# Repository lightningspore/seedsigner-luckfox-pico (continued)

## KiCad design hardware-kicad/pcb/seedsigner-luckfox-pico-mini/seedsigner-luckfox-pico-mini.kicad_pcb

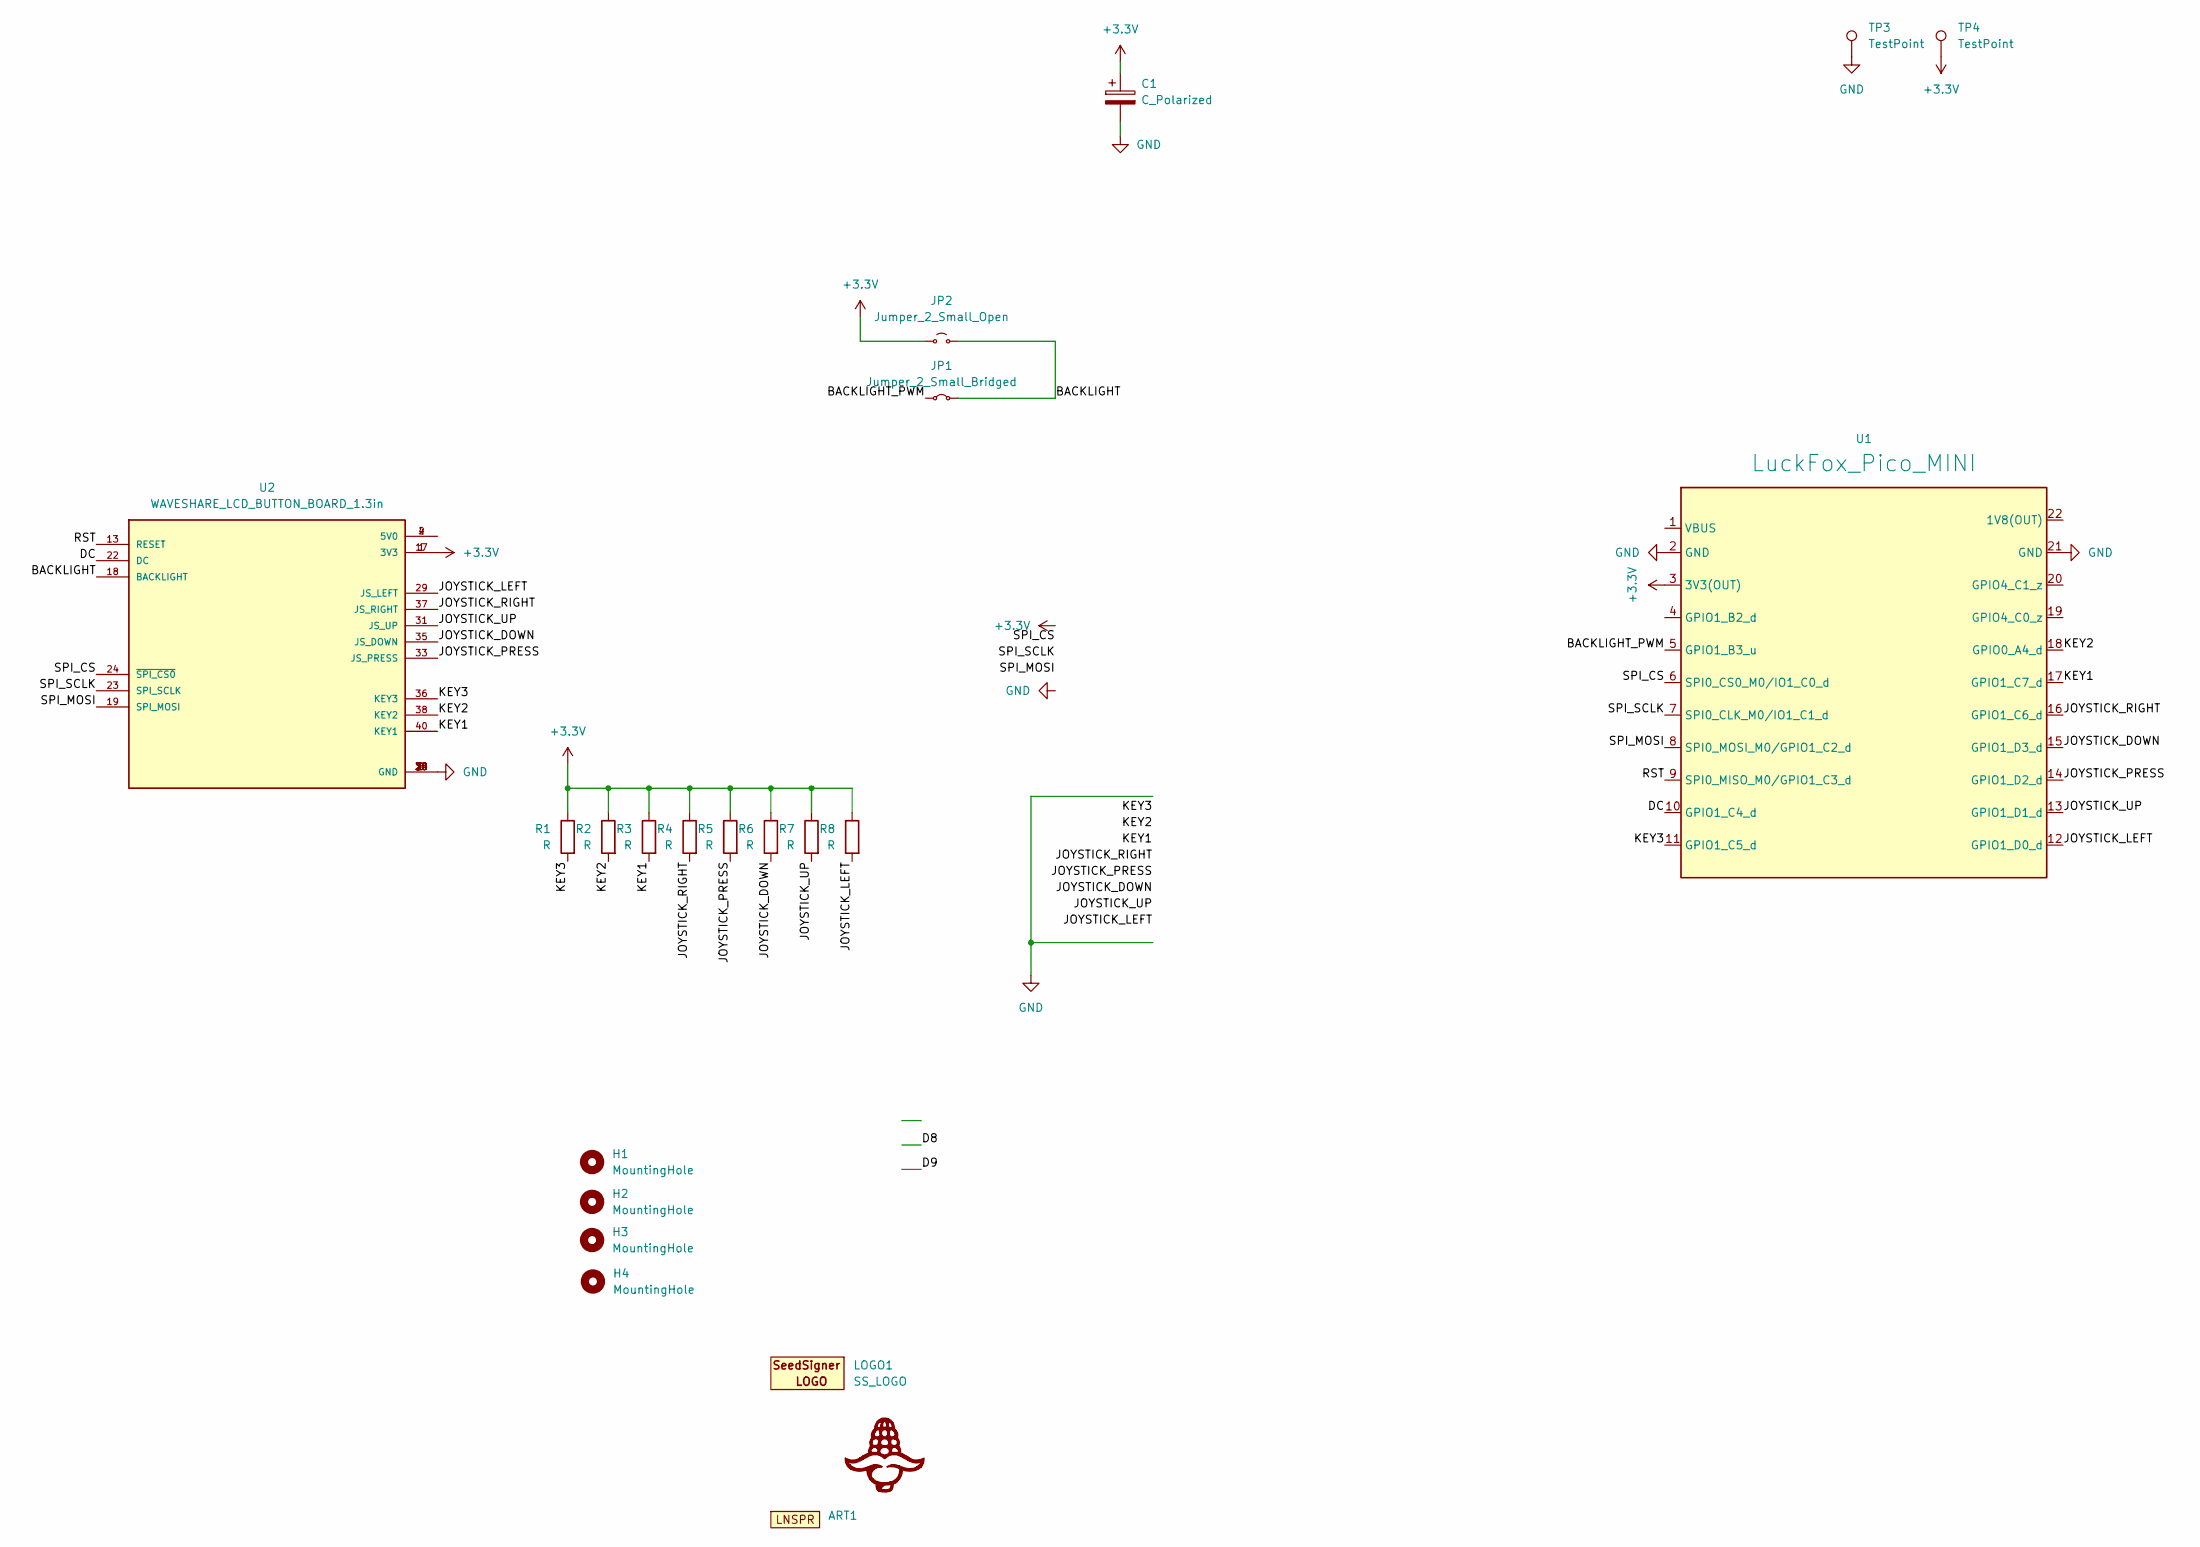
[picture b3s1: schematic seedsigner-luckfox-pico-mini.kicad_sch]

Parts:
ART1: LightningSpore_Logo
C1: C_Polarized; CP_Radial_D5.0mm_P2.50mm
H1, H2, H3, H4: MountingHole; MOUNT_HOLE_3MM
JP1: Jumper_2_Small_Bridged; SolderJumper-2_P1.3mm_Bridged_Pad1.0x1.5mm
JP2: Jumper_2_Small_Open; SolderJumper-2_P1.3mm_Open_Pad1.0x1.5mm
LOGO1: SS_LOGO; seedsigner-logo-small
LOGO2: CORN-LOGO; corn-logo
R1, R2, R3, R4, R5, R6, R7, R8: R; R_0603_1608Metric_Pad0.98x0.95mm_HandSolder
TP3, TP4: TestPoint; TestPoint_Pad_1.5x1.5mm
U1: LuckFox_Pico_MINI; LUCKFOX_PICO_MINI
U2: WAVESHARE_LCD_BUTTON_BOARD_1.3in; WAVESHARE_LCD_BUTTON

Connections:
+3.3V: C1.1, JP2.1 (A), R1.1, R2.1, R3.1, R4.1, R5.1, R6.1, R7.1, R8.1, TP4.1, U1.3 (3V3(OUT)), U2.1 (3V3), U2.17 (3V3)
/BACKLIGHT: JP1.2 (B), JP2.2 (B), U2.18 (BACKLIGHT)
/BACKLIGHT_PWM: JP1.1 (A), U1.5 (GPIO1_B3_u)
/DC: U1.10 (GPIO1_C4_d), U2.22 (DC)
/JOYSTICK_DOWN: R6.2, U1.15 (GPIO1_D3_d), U2.35 (JS_DOWN)
/JOYSTICK_LEFT: R8.2, U1.12 (GPIO1_D0_d), U2.29 (JS_LEFT)
/JOYSTICK_PRESS: R5.2, U1.14 (GPIO1_D2_d), U2.33 (JS_PRESS)
/JOYSTICK_RIGHT: R4.2, U1.16 (GPIO1_C6_d), U2.37 (JS_RIGHT)
/JOYSTICK_UP: R7.2, U1.13 (GPIO1_D1_d), U2.31 (JS_UP)
/KEY1: R3.2, U1.17 (GPIO1_C7_d), U2.40 (KEY1)
/KEY2: R2.2, U1.18 (GPIO0_A4_d), U2.38 (KEY2)
/KEY3: R1.2, U1.11 (GPIO1_C5_d), U2.36 (KEY3)
/RST: U1.9 (SPI0_MISO_M0/GPIO1_C3_d), U2.13 (RESET)
/SPI_CS: U1.6 (SPI0_CS0_M0/IO1_C0_d), U2.24 (~SPI_CS0)
/SPI_MOSI: U1.8 (SPI0_MOSI_M0/GPIO1_C2_d), U2.19 (SPI_MOSI)
/SPI_SCLK: U1.7 (SPI0_CLK_M0/IO1_C1_d), U2.23 (SPI_SCLK)
GND: C1.2, TP3.1, U1.2 (GND), U1.21 (GND), U2.6 (GND), U2.9 (GND), U2.14 (GND), U2.20 (GND), U2.25 (GND), U2.30 (GND), U2.34 (GND), U2.39 (GND)
unnamed: U2.2 (5V0), U2.4 (5V0)

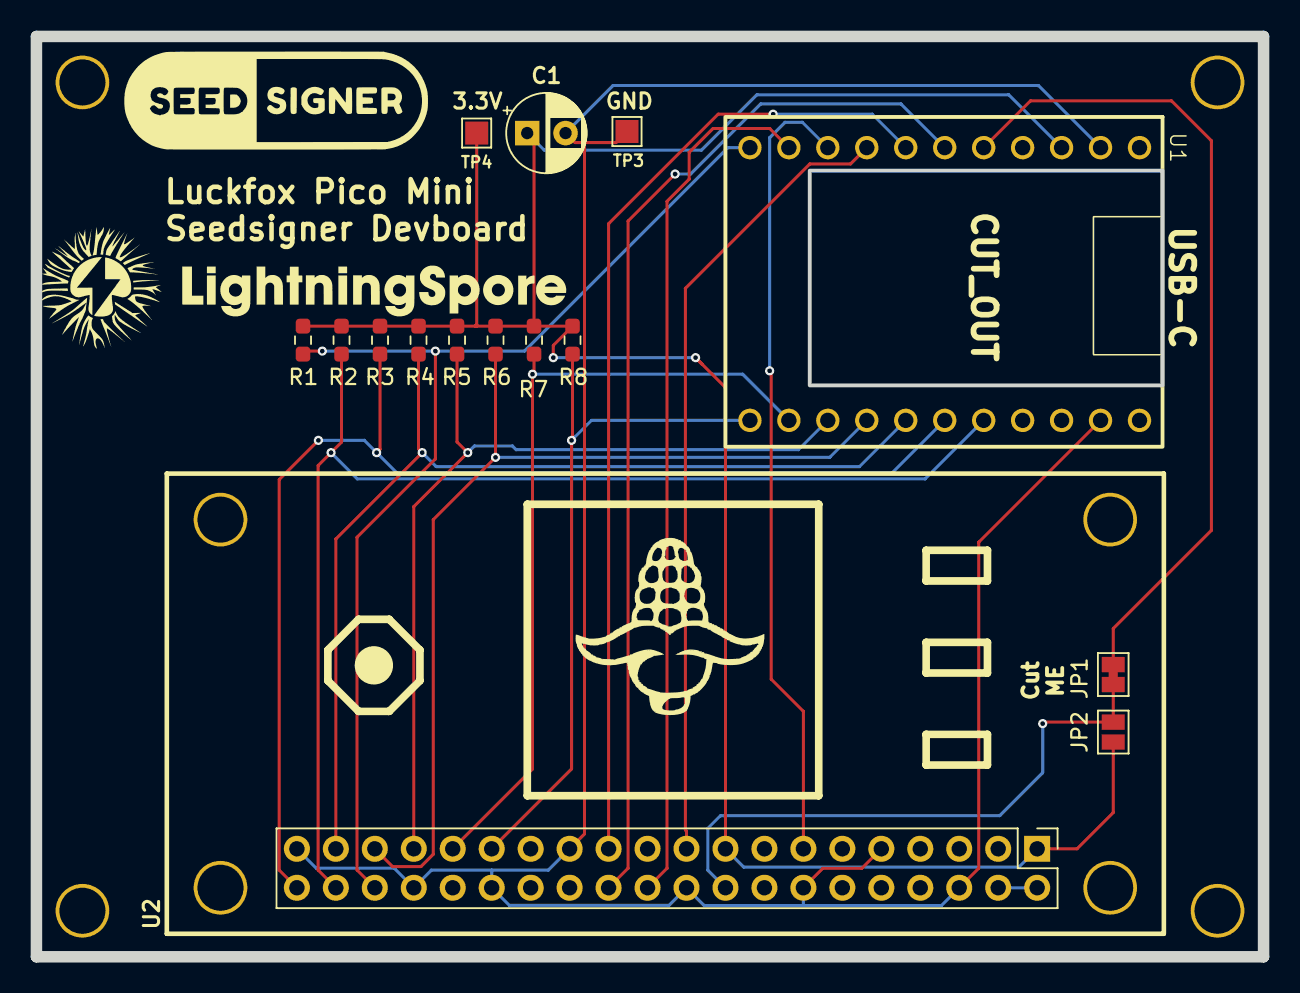
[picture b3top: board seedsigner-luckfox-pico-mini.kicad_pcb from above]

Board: 2 copper layers, 80.0 x 60.0 mm, 22 parts (0 on the bottom side), 18 nets.

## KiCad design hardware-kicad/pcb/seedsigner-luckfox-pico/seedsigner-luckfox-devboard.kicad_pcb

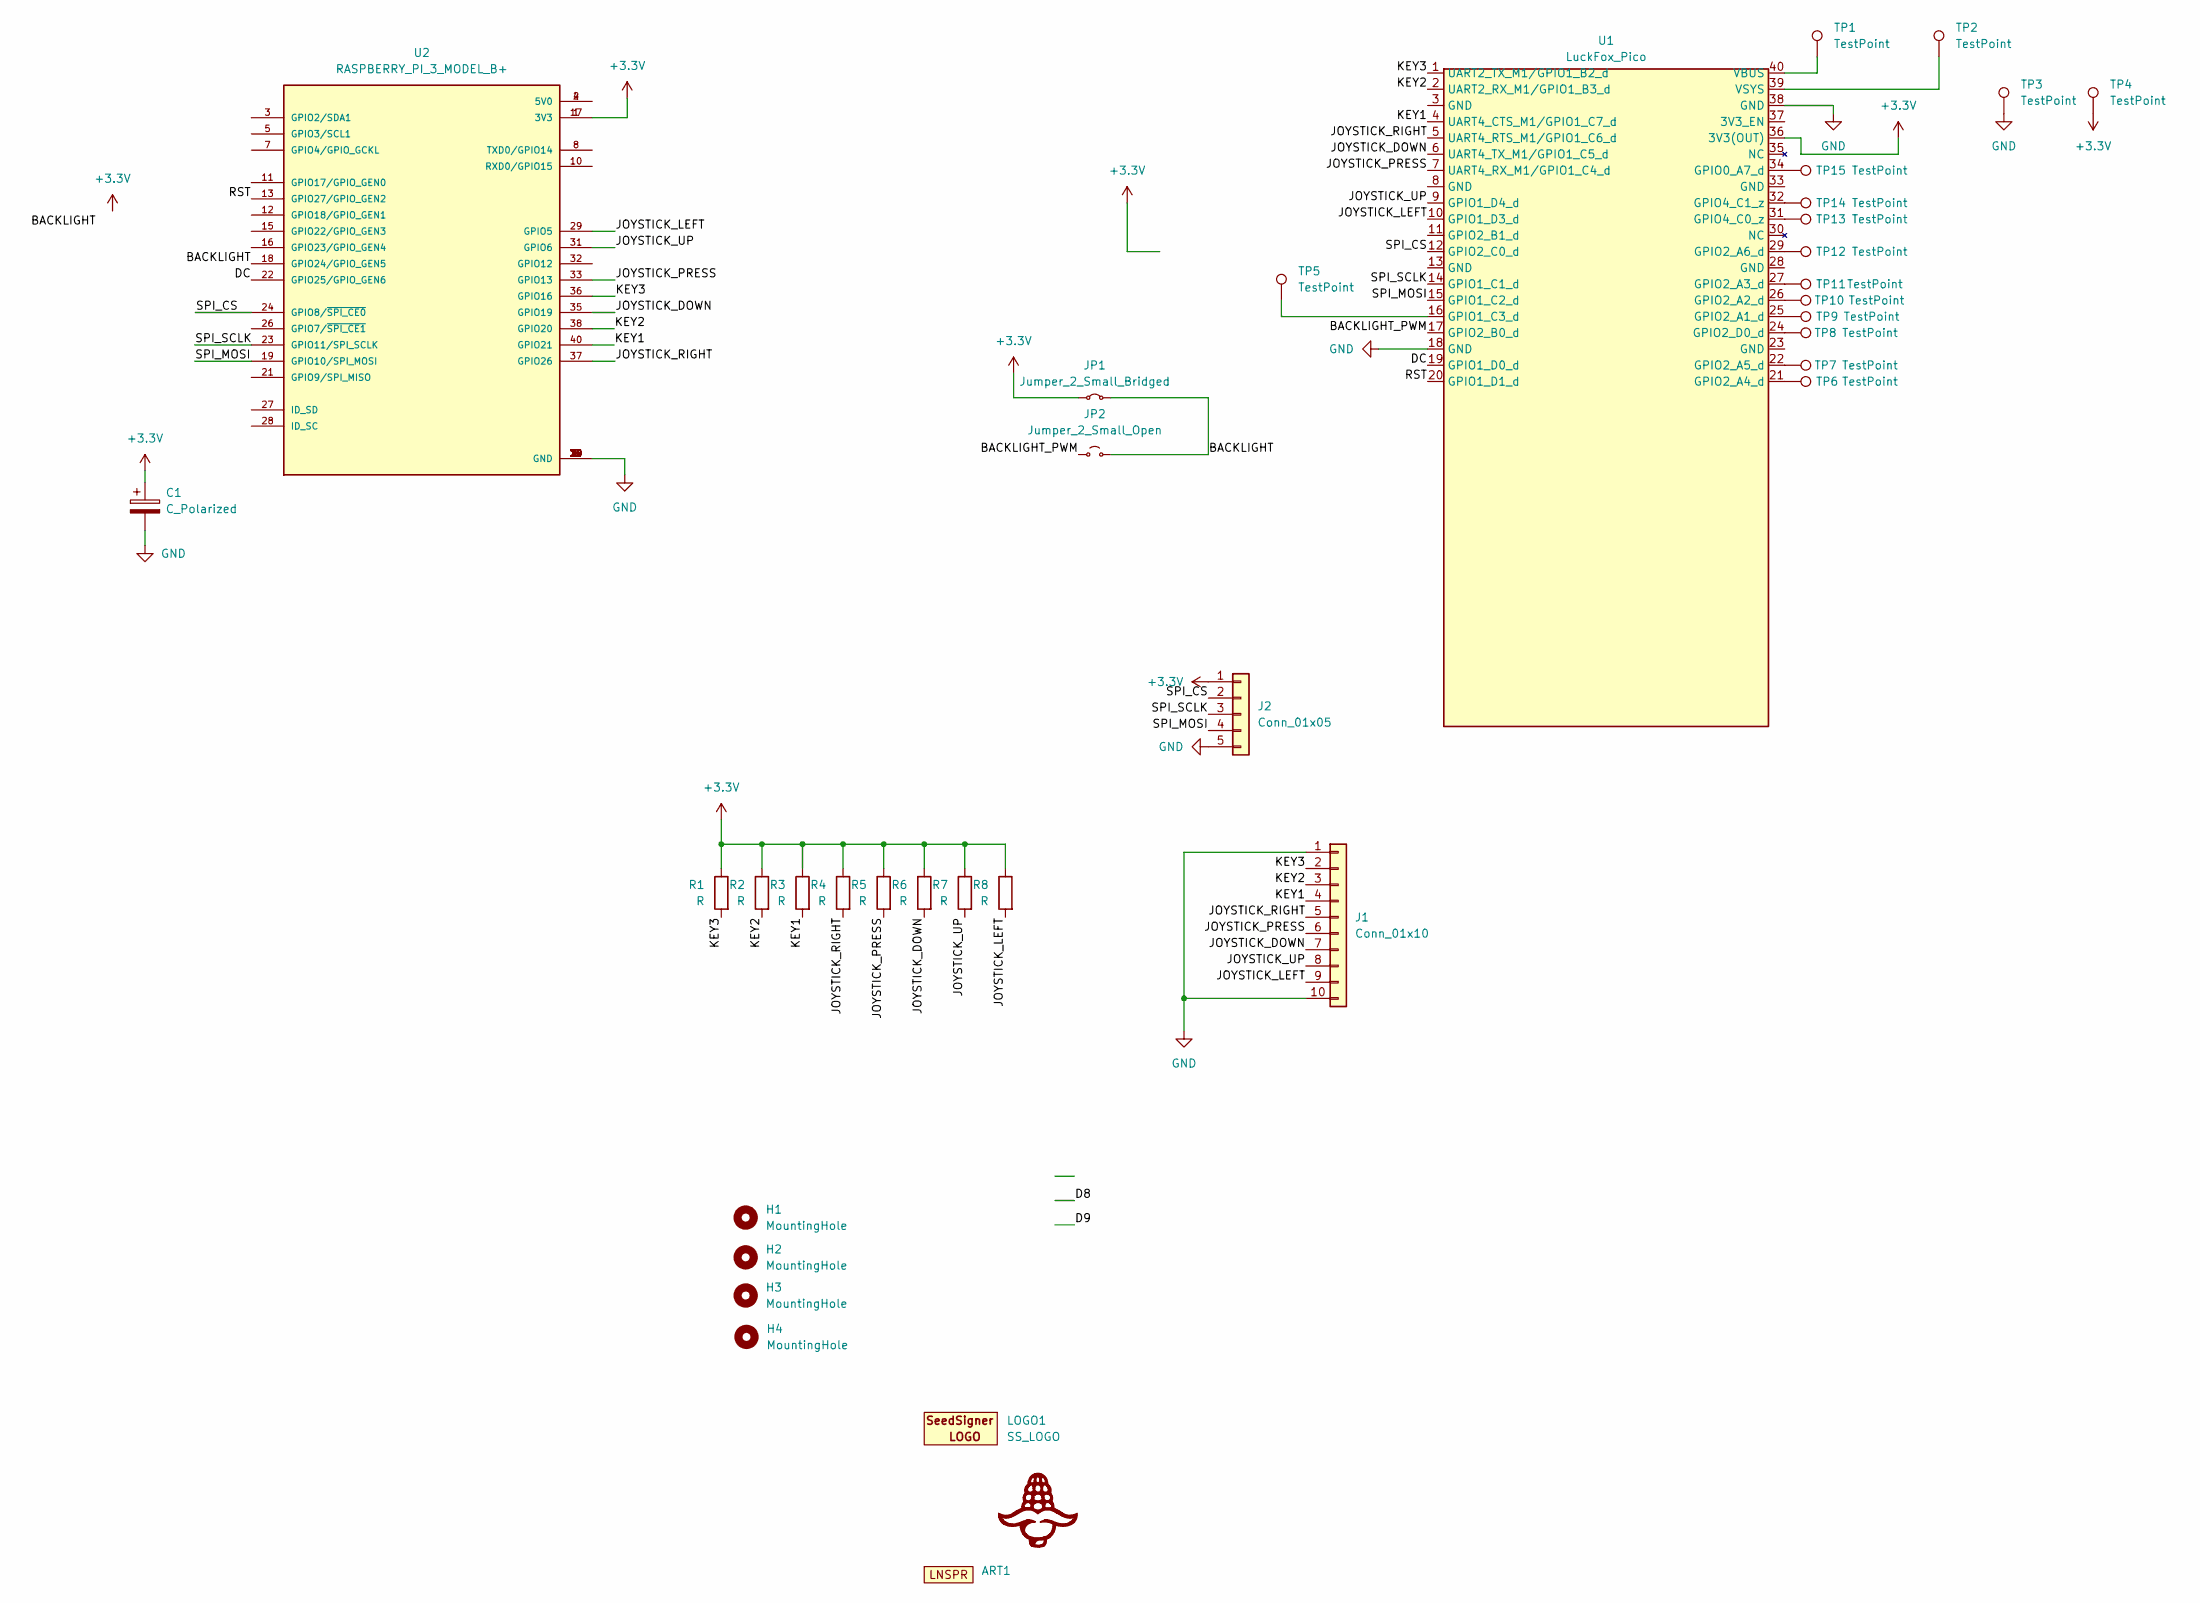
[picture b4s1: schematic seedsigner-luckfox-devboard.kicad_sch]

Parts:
ART1: LightningSpore_Logo
C1: C_Polarized; CP_Radial_D5.0mm_P2.50mm
H1, H2, H3, H4: MountingHole; MOUNT_HOLE_3MM
J1: Conn_01x10; PinHeader_1x10_P2.54mm_Horizontal
J2: Conn_01x05; PinHeader_1x05_P2.54mm_Horizontal
JP1: Jumper_2_Small_Bridged; SolderJumper-2_P1.3mm_Bridged_Pad1.0x1.5mm
JP2: Jumper_2_Small_Open; SolderJumper-2_P1.3mm_Open_Pad1.0x1.5mm
LOGO1: SS_LOGO; seedsigner-logo-small
LOGO2: CORN-LOGO; corn-logo
R1, R2, R3, R4, R5, R6, R7, R8: R; R_2512_6332Metric
TP1, TP2, TP3, TP4, TP5, TP6, TP7, TP8, TP9, TP10, TP11, TP12, TP13, TP14, TP15: TestPoint; TestPoint_Pad_1.5x1.5mm
U1: LuckFox_Pico; LUCKFOX_PICO_PRO_MAX_PTH
U2: RASPBERRY_PI_3_MODEL_B+; WAVESHARE_LCD_BUTTON; PARTREV 1.0

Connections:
+3.3V: C1.1, J2.1, JP1.1 (A), R1.1, R2.1, R3.1, R4.1, R5.1, R6.1, R7.1, R8.1, TP4.1, U1.36 (3V3(OUT)), U2.1 (3V3), U2.17 (3V3)
/BACKLIGHT: JP1.2 (B), JP2.2 (B), U2.18 (GPIO24/GPIO_GEN5)
/BACKLIGHT_PWM: JP2.1 (A), U1.17 (GPIO2_B0_d)
/DC: U1.19 (GPIO1_D0_d), U2.22 (GPIO25/GPIO_GEN6)
/JOYSTICK_DOWN: J1.7, R6.2, U1.6 (UART4_TX_M1/GPIO1_C5_d), U2.35 (GPIO19)
/JOYSTICK_LEFT: J1.9, R8.2, U1.10 (GPIO1_D3_d), U2.29 (GPIO5)
/JOYSTICK_PRESS: J1.6, R5.2, U1.7 (UART4_RX_M1/GPIO1_C4_d), U2.33 (GPIO13)
/JOYSTICK_RIGHT: J1.5, R4.2, U1.5 (UART4_RTS_M1/GPIO1_C6_d), U2.37 (GPIO26)
/JOYSTICK_UP: J1.8, R7.2, U1.9 (GPIO1_D4_d), U2.31 (GPIO6)
/KEY1: J1.4, R3.2, U1.4 (UART4_CTS_M1/GPIO1_C7_d), U2.40 (GPIO21)
/KEY2: J1.3, R2.2, U1.2 (UART2_RX_M1/GPIO1_B3_d), U2.38 (GPIO20)
/KEY3: J1.2, R1.2, U1.1 (UART2_TX_M1/GPIO1_B2_d), U2.36 (GPIO16)
/RST: U1.20 (GPIO1_D1_d), U2.13 (GPIO27/GPIO_GEN2)
/SPI_CS: J2.2, U1.12 (GPIO2_C0_d), U2.24 (GPIO8/~SPI_CE0)
/SPI_MOSI: J2.4, U1.15 (GPIO1_C2_d), U2.19 (GPIO10/SPI_MOSI)
/SPI_SCLK: J2.3, U1.14 (GPIO1_C1_d), U2.23 (GPIO11/SPI_SCLK)
GND: C1.2, J1.1, J1.10, J2.5, TP3.1, U1.18 (GND), U1.38 (GND), U2.6 (GND), U2.9 (GND), U2.14 (GND), U2.20 (GND), U2.25 (GND), U2.30 (GND), U2.34 (GND), U2.39 (GND)
unnamed: TP15.1, U1.34 (GPIO0_A7_d)
unnamed: TP5.1, U1.16 (GPIO1_C3_d)
unnamed: TP9.1, U1.25 (GPIO2_A1_d)
unnamed: TP10.1, U1.26 (GPIO2_A2_d)
unnamed: TP11.1, U1.27 (GPIO2_A3_d)
unnamed: TP6.1, U1.21 (GPIO2_A4_d)
unnamed: TP7.1, U1.22 (GPIO2_A5_d)
unnamed: TP12.1, U1.29 (GPIO2_A6_d)
unnamed: TP8.1, U1.24 (GPIO2_D0_d)
unnamed: TP13.1, U1.31 (GPIO4_C0_z)
unnamed: TP14.1, U1.32 (GPIO4_C1_z)
unnamed: TP1.1, U1.40 (VBUS)
unnamed: TP2.1, U1.39 (VSYS)
unnamed: U2.2 (5V0), U2.4 (5V0)

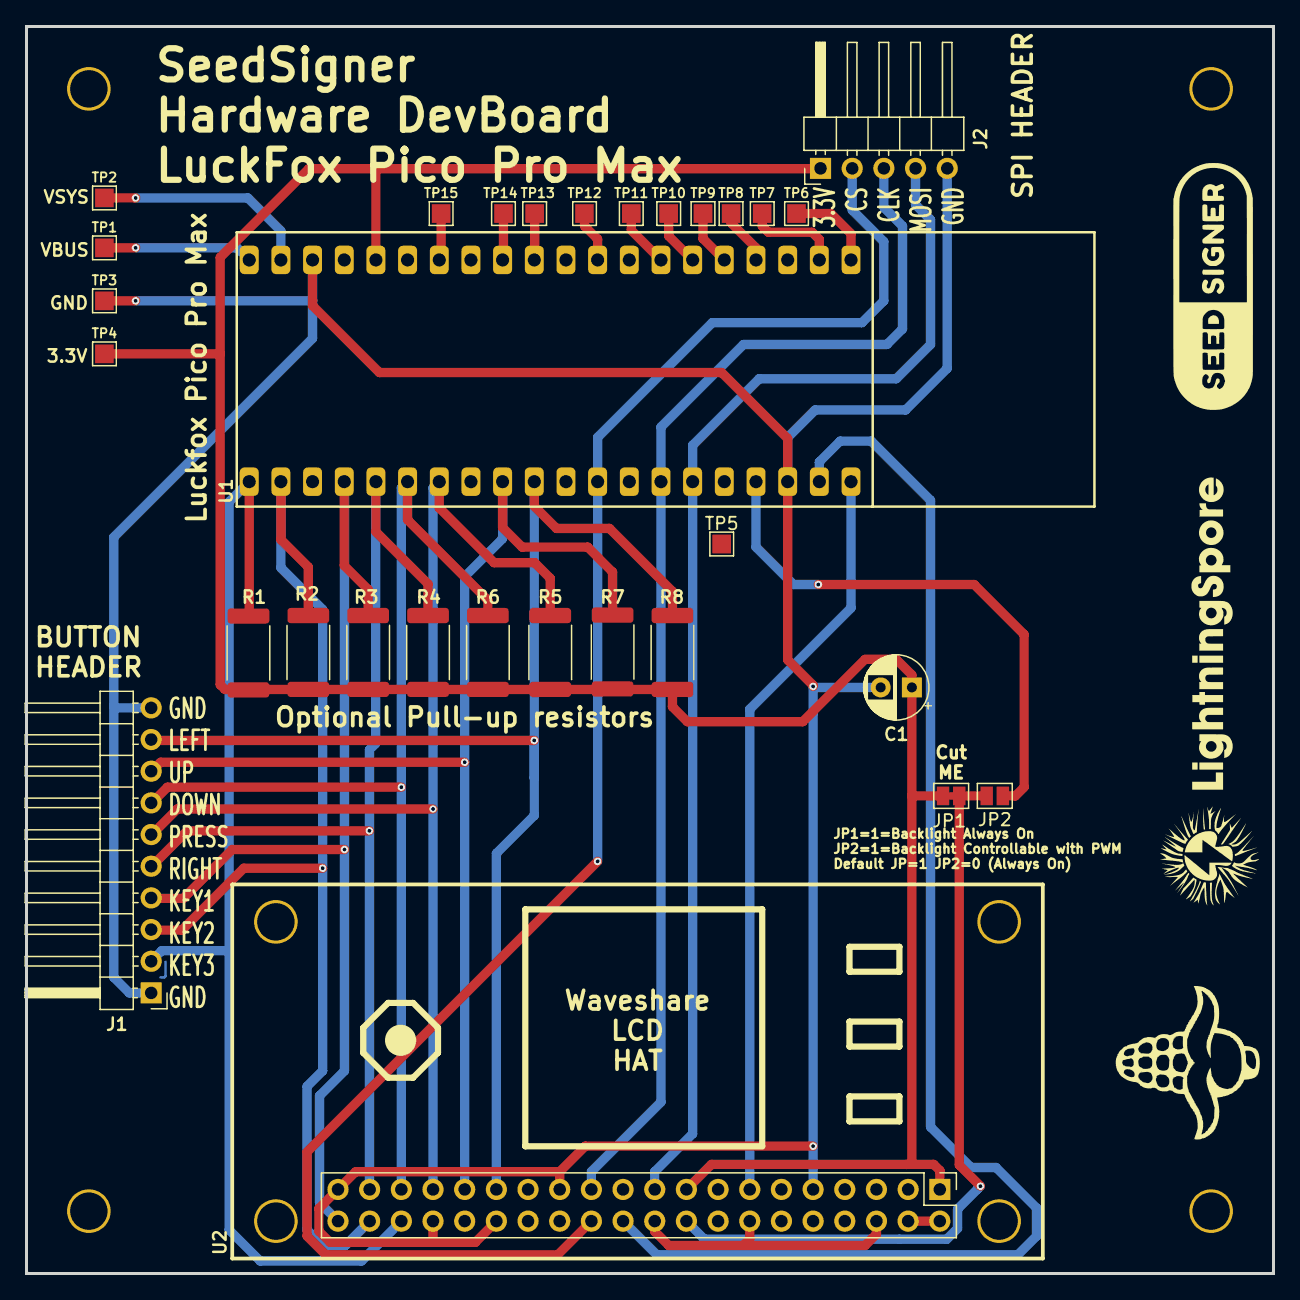
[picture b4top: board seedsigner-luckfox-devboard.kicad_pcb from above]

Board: 2 copper layers, 100.0 x 100.0 mm, 37 parts (0 on the bottom side), 31 nets.

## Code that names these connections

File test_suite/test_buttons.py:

import time

from periphery import GPIO


pin_LEFT = GPIO(42, "in")  # LEFT  # yes-pullup
pin_RIGHT = GPIO(43, "in") # RIGHT # yes-pullup
pin_UP = GPIO(55, "in")    # UP    # no-pullup
pin_DOWN = GPIO(54, "in")  # DOWN  # no-pullup

pin_ENTER = GPIO(53, "in") # PRESS # no-pullup

pin_KEY1 = GPIO(52, "in")  # KEY1  # no-pullup
pin_KEY2 = GPIO(58, "in")  # KEY2  # no-pullup
pin_KEY3 = GPIO(59, "in")  # KEY3  # no-pullup

val = pin_KEY3.read()


pins = [
    ("LEFT", pin_LEFT),
    ("RIGHT", pin_RIGHT),
    ("UP", pin_UP),
    ("DOWN", pin_DOWN),
    ("ENTER", pin_ENTER),
    ("KEY1", pin_KEY1),
    ("KEY2", pin_KEY2),
    ("KEY3", pin_KEY3)
]

for name, pin in pins:
    print(f"Press the {name} button and then press Enter")
    while pin.read():
        pass
    input("Button pressed, press Enter to continue...")
    print(f"{name} button confirmed working")
    time.sleep(0.5)

print("All buttons confirmed working")

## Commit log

2024-06-15 working on the the lcd screen
2024-08-13 basic working version, no camera!
2024-11-25 beginning of test suite
2024-11-25 test suite beginning
2024-11-27 script for creating flashable OS images
2024-12-05 buildroot config file
2024-12-05 add kicad test-harness design files
2024-12-05 image create and flash tools
2024-12-05 update path in test_lcd
2024-12-05 hardware config
2024-12-05 Issac First Commit
2024-12-05 more install readme
2024-12-17 commit doc
2024-12-17 slight update
2024-12-17 Properly Mapped Buttons
    test_buttons_lcd.py Is a new script that will display the buttons name on the lcd when pressed.
2024-12-17 Camera to LCD success
    test_all.py successfully takes a picture when the KEY1 button is pressed then displays the picture on the LCD screen
2024-12-17 UX test completed
    UX test called test.py is a script that allows user to test all buttons, camera, and exit test.
2024-12-17 buildroot needs to build
2024-12-17 more installation steps
2024-12-17 dockerfile noninteractive apt
2024-12-18 use custom font in test suite
2024-12-18 copy config history
2024-12-18 add test qrcode
2024-12-18 python dep package
2024-12-18 readme and install tools update
2024-12-18 working buildroot config
2024-12-18 steps to run the seedsigner code
2024-12-18 delete
2024-12-19 more setup steps
2024-12-21 update hash for pyzbar
2024-12-30 final scripts for fully working installation
2024-12-30 more commands and docs
2025-01-13 add autostart script
2025-03-10 improve buildroot OS build steps
2025-03-10 more OS build instructions
2025-03-19 add tools to compile buildroot images into a flashable version
2025-03-19 buildroot SS package select
2025-03-23 further automatic setup of the OS build
    install the pin config and copy over seedsigner code
    when entering the container setup the environment so we can directly start doing buildroot
2025-03-23 Update readme with images of the prototype device
2025-03-23 Add BOM with total costs and demo video link
2025-04-21 improve readability of readme
2025-04-21 more readability changes
2025-05-07 continue to improve OS build process
2025-05-07 cleanup and document
2025-05-08 approaching a working build
2025-05-08 it works, start seedsigner on boot
2025-05-15 fix kicad files and upload gerbers
2025-05-15 export footprint library pretty files, and update pcb to use library
2025-05-15 Add luckfox 3d models and start Luckfox pico mini footprint
2025-05-15 update libraries and make schematic and pcb only use parts from library
2025-05-15 update the sch/pcb to kiCAD 9
2025-05-16 restructure dir structure and start luckfox-pico-mini pcb
2025-05-17 add waveshare lcd 3d model and initial pcb routing
2025-05-19 add buy-me-a-coffee link to README
2025-05-26 small docs change
2025-05-26 restart pcb from backup
2025-05-26 dont commit lockfiles, delete used repo
2025-05-26 auto-route and cleanup of pico mini devboard
2025-05-26 add pdf schematic of pico pro max dev board
2025-05-26 add a github action to run automated builds of the OS
2025-05-27 finalize luckfox pico mini design
2025-05-27 waveshare lcd+button hat 3d models
2025-05-27 commit gerbers and last mods of luckfox mini pcb
2025-06-10 cleanup project paths and make sure symbols and footprints are committed
2025-06-18 Update README with info about OS/kernel changes for this project
2025-06-18 closer and closer to an automated OS build
2025-06-18 Add RPi Zero footprint to library
2025-06-18 start seedsigner-hardware-dev-v1 PCB
2025-06-18 seedsigner hardware dev v1 all footprints created and placed
2025-06-19 hardware devboard changes and footprints for LCD screens
2025-06-20 lets get automated buildroot working
2025-06-21 almost foolproof images
2025-06-23 Cleanup README and shopping list
2025-06-23 use hierarchical sheets in kicad
2025-06-23 more pics in the shopping list
2025-06-23 luckfox pico mini photos
2025-06-30 cleanup readme and move buildroot doc
2025-06-30 more buildroot folder structure changes
2025-06-30 os builds are building properly automatically
2025-06-30 update library paths and modularize sch
2025-06-30 autoroute the hardware devboard
2025-07-01 Kicad work related to new PCB
2025-07-01 create individual test files to test the hardware
2025-07-03 test suite: record camera capture
2025-07-08 2 different pcbs almost done
2025-07-08 close to ordering on jlcpcb
2025-07-09 ordered seedsigner-hardware-dev-v1 from jlcpcb
2025-07-26 pcb checkin, ordered
2025-07-26 goosify automatic builds
2025-07-26 cleanup and consolidate all build scripts
2025-07-26 remove emojis and some cleanup
2025-07-27 build: dont pollute the filesystem
2025-07-27 cleanup dockerfile, remove redundant scripts
2025-07-28 enhance build process: automate artifact availability and update documentation. Fix github actions.
2025-07-28 Require x86_64 to build
2025-07-28 Improve github actions artifacts upload
